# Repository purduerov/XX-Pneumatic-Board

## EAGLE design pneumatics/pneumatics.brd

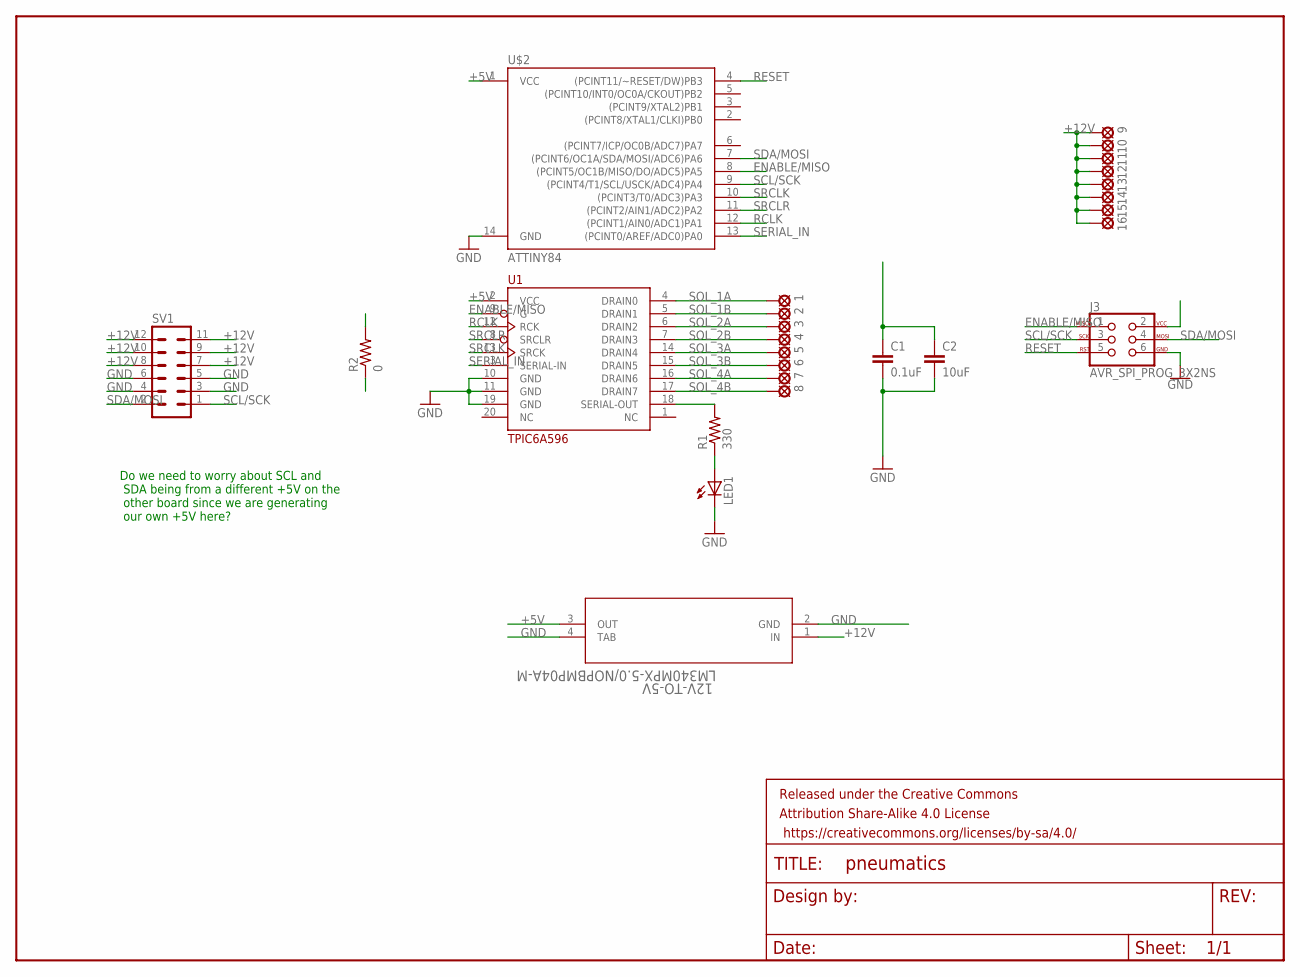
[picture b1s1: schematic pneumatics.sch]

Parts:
1, 2, 3, 4, 5, 6, 7, 8, 9, 10, 11, 12, 13, 14, 15, 16: SE14
12V-TO-5V: LM340MPX-5.0/NOPBMP04A-M; MP04A-M
C1: 0.1uF; 0603-CAP
C2: 10uF; 0603-CAP
FRAME1: FRAME-LETTERNO_PACKAGE; DUMMY
J3: AVR_SPI_PROG_3X2NS; 2X3-NS
LED1: LED_ESML0603; LED_SML0603
R1: 330; R0603
R2: 0; R0603
SV1: MA06-2
U1: TPIC6A596; SOIC20-W
U$2: ATTINY84; SO14

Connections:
+5V: 12V-TO-5V.3 (OUT), C1.1, C2.1, J3.2, U1.2 (VCC), U$2.1 (VCC)
+12V: 9.MP, 10.MP, 11.MP, 12.MP, 12V-TO-5V.1 (IN), 13.MP, 14.MP, 15.MP, 16.MP, SV1.7, SV1.8, SV1.9, SV1.10, SV1.11, SV1.12
ENABLE/MISO: J3.1, U1.9 (G), U$2.8 ((PCINT5/OC1B/MISO/DO/ADC5)PA5)
GND: 12V-TO-5V.2 (GND), 12V-TO-5V.4 (TAB), C1.2, C2.2, J3.6, LED1.C, SV1.3, SV1.4, SV1.5, SV1.6, U1.10 (GND), U1.11 (GND), U1.19 (GND), U$2.14 (GND)
unnamed: R1.2, U1.18 (SERIAL-OUT)
unnamed: LED1.A, R1.1
RCLK: R2.2, U1.12 (RCK), U$2.12 ((PCINT1/AIN0/ADC1)PA1)
RESET: J3.5, U$2.4 ((PCINT11/~RESET/DW)PB3)
SCL/SCK: J3.3, SV1.1, U$2.9 ((PCINT4/T1/SCL/USCK/ADC4)PA4)
SDA/MOSI: J3.4, SV1.2, U$2.7 ((PCINT6/OC1A/SDA/MOSI/ADC6)PA6)
SERIAL_IN: U1.3 (SERIAL-IN), U$2.13 ((PCINT0/AREF/ADC0)PA0)
SOL_1A: 1.MP, U1.4 (DRAIN0)
SOL_1B: 2.MP, U1.5 (DRAIN1)
SOL_2A: 3.MP, U1.6 (DRAIN2)
SOL_2B: 4.MP, U1.7 (DRAIN3)
SOL_3A: 5.MP, U1.14 (DRAIN4)
SOL_3B: 6.MP, U1.15 (DRAIN5)
SOL_4A: 7.MP, U1.16 (DRAIN6)
SOL_4B: 8.MP, U1.17 (DRAIN7)
SRCLK: R2.1, U1.13 (SRCK), U$2.10 ((PCINT3/T0/ADC3)PA3)
SRCLR: U1.8 (SRCLR), U$2.11 ((PCINT2/AIN1/ADC2)PA2)

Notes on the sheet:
Do we need to worry about SCL and SDA being from a different +5V on the other board since we are generating our own +5V here?

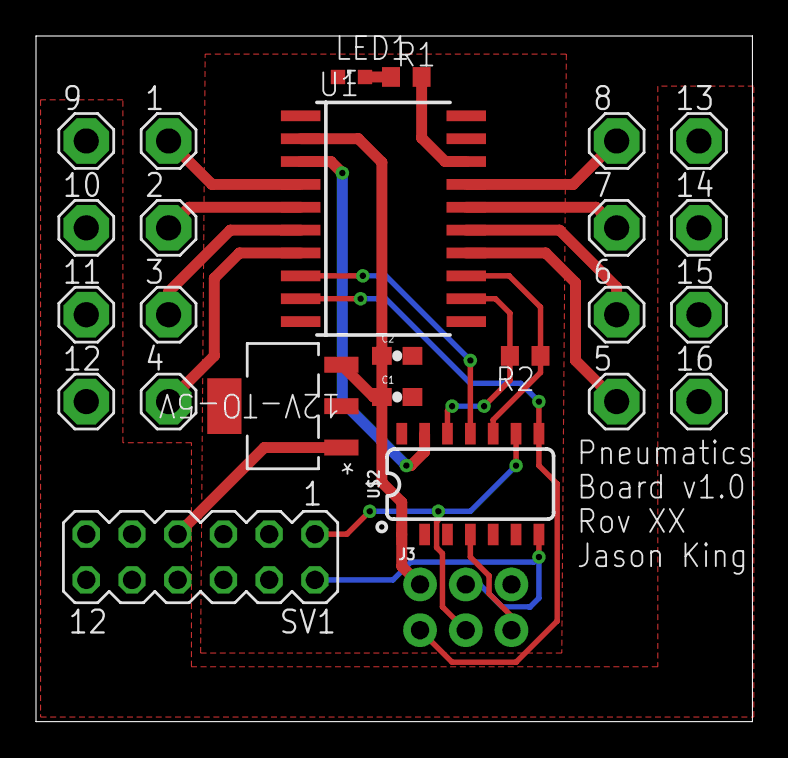
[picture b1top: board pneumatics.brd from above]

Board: 2 copper layers, 39.8 x 38.1 mm, 27 parts (0 on the bottom side), 21 nets.

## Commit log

2017-12-27 Added empty project
2017-12-27 Theoretically finished the schematic
2017-12-27 Added brd before dinner
2017-12-28 Intermediate board
2017-12-28 Done?
2017-12-28 Fixed text on silk screen

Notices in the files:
parts and their libraries:
SparkFun-Passives: Licensing: CC v3.0 Share-Alike You are welcome to use this library for commercial purposes.
SparkFun-Aesthetics: Licensing: Creative Commons ShareAlike 4.0 International - https://creativecommons.org/licenses/by-sa/4.0
SparkFun-Aesthetics: Released under the Creative Commons
